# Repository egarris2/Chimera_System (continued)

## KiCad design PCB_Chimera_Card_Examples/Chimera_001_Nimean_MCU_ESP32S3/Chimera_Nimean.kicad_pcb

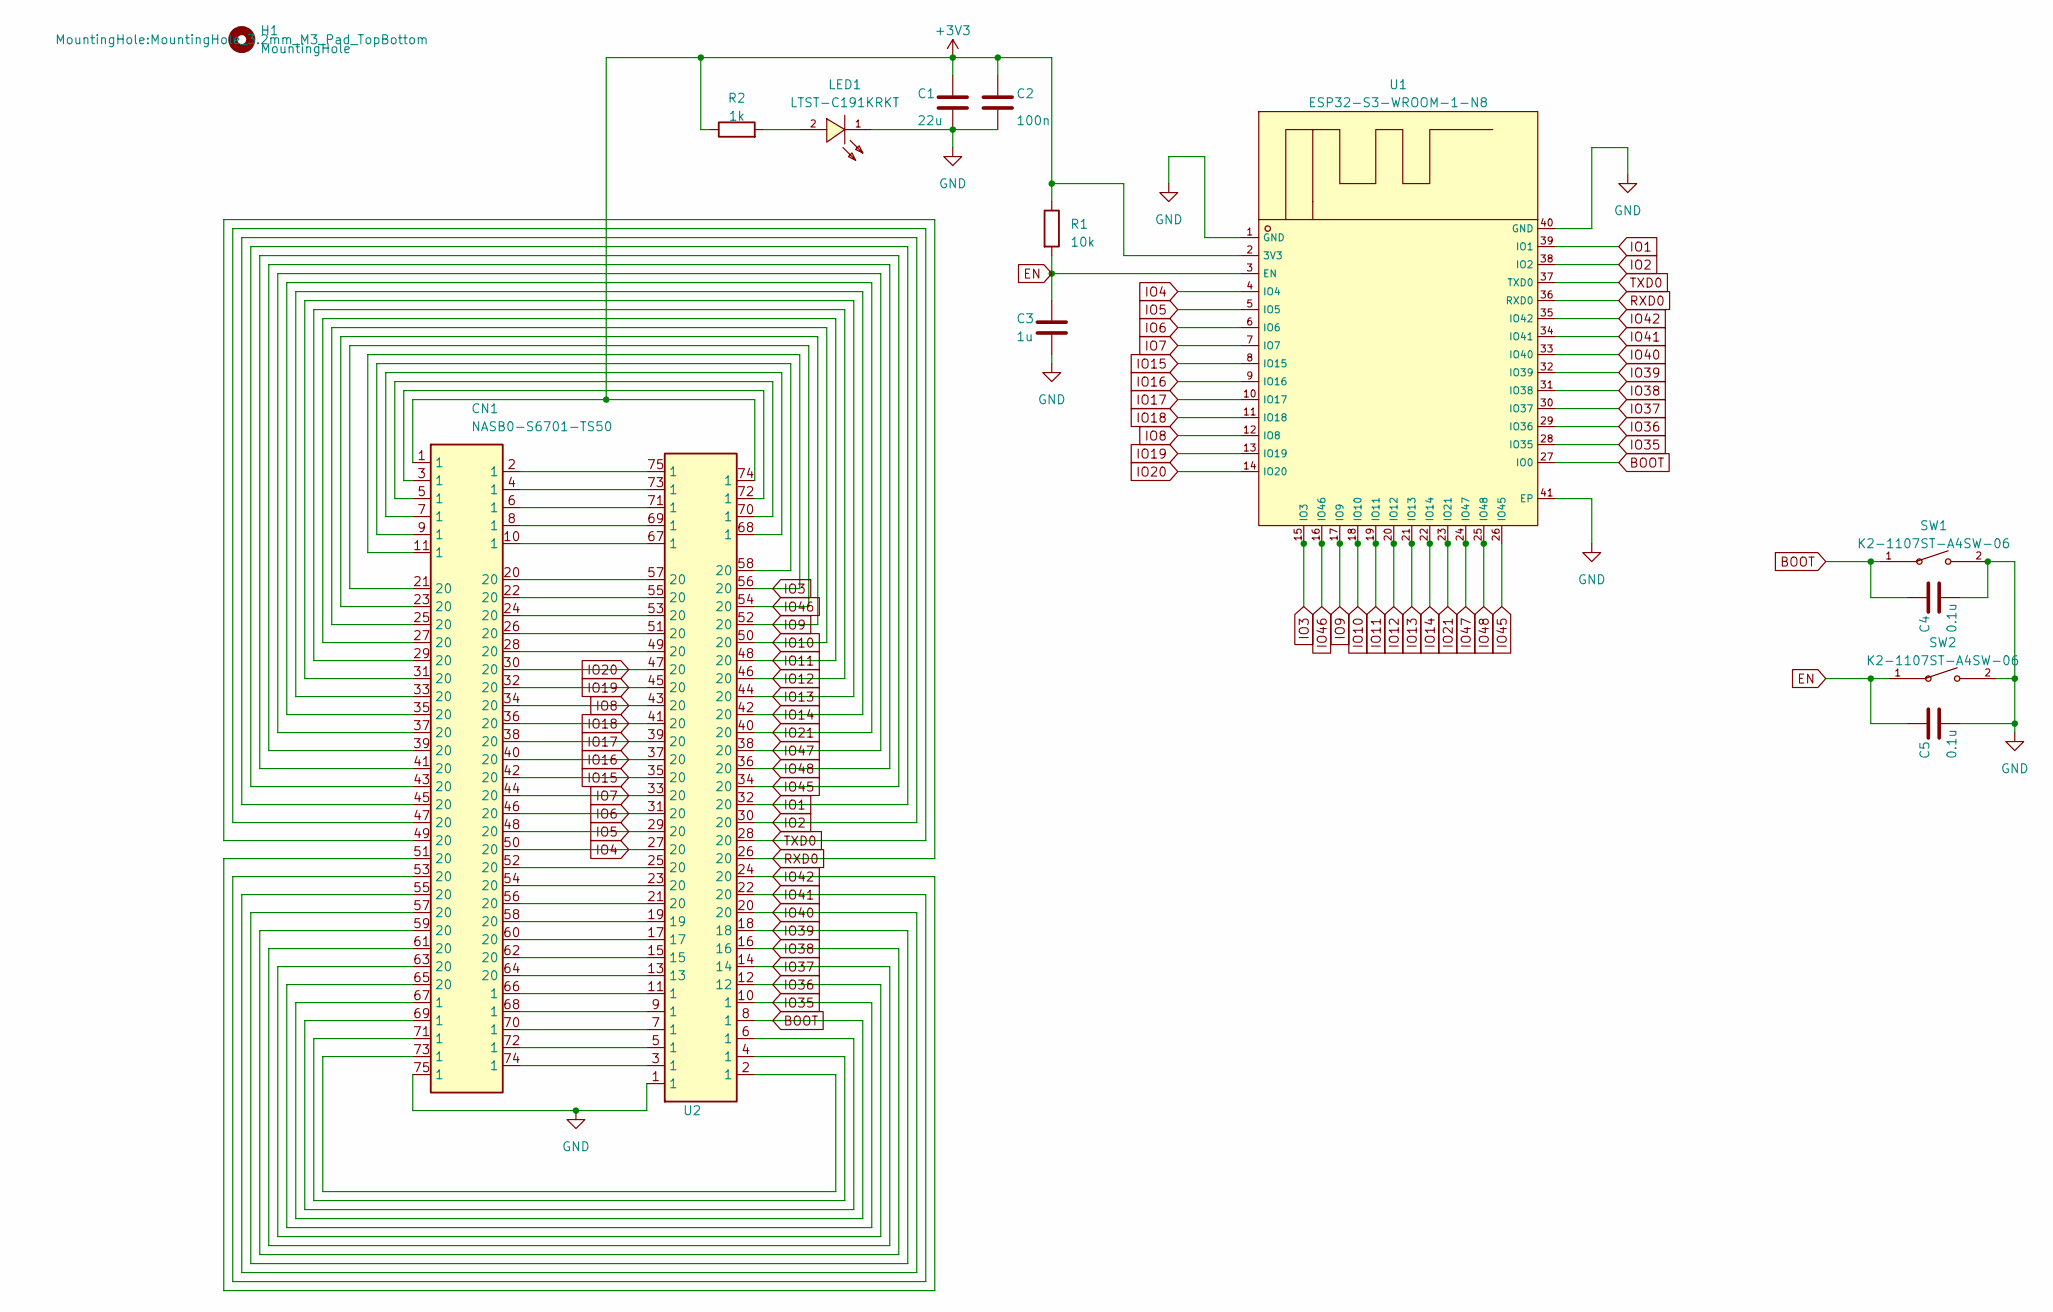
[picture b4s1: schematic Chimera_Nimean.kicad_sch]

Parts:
C1: 22u; C_0603_1608Metric
C2: 100n; C_0603_1608Metric
C3: 1u; C_0603_1608Metric
C4, C5: 0.1u; C_0603_1608Metric
CN1: NASB0-S6701-TS50; CONN-SMD_67P-P0.50-V_NASB0-S6701-TS50; LCSC C367024
H1: MountingHole; MountingHole_3.2mm_M3_Pad_TopBottom
LED1: LTST-C191KRKT; LED0603-RD; LCSC C125099
R1: 10k; R_0603_1608Metric
R2: 1k; R_0603_1608Metric
SW1, SW2: K2-1107ST-A4SW-06; KEY-SMD_L6.2-W3.6-LS8.0; LCSC C118141
U1: ESP32-S3-WROOM-1-N8; WIFIM-SMD_ESP32-S3-WROOM-1-N8; LCSC C2913198
U2: NGFF_M

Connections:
+3V3: C1.1, C2.1, CN1.1, R1.1, R2.1, U1.2 (3V3), U2.74 (1)
BOOT: C4.1, CN1.67 (1), SW1.1, U1.27 (IO0), U2.8 (1)
EN: C3.1, C5.1, R1.2, SW2.1, U1.3 (EN)
GND: C1.2, C2.2, C3.2, C4.2, C5.2, CN1.75 (1), LED1.1 (-), SW1.2, SW2.2, U1.1 (GND), U1.40 (GND), U1.41 (EP), U2.1
IO1: CN1.43 (20), U1.39 (IO1), U2.32 (20)
IO2: CN1.45 (20), U1.38 (IO2), U2.30 (20)
IO3: CN1.11 (1), U1.15 (IO3), U2.56 (20)
IO4: CN1.50 (20), U1.4 (IO4), U2.27 (20)
IO5: CN1.48 (20), U1.5 (IO5), U2.29 (20)
IO6: CN1.46 (20), U1.6 (IO6), U2.31 (20)
IO7: CN1.44 (20), U1.7 (IO7), U2.33 (20)
IO8: CN1.34 (20), U1.12 (IO8), U2.43 (20)
IO9: CN1.23 (20), U1.17 (IO9), U2.52 (20)
IO10: CN1.25 (20), U1.18 (IO10), U2.50 (20)
IO11: CN1.27 (20), U1.19 (IO11), U2.48 (20)
IO12: CN1.29 (20), U1.20 (IO12), U2.46 (20)
IO13: CN1.31 (20), U1.21 (IO13), U2.44 (20)
IO14: CN1.33 (20), U1.22 (IO14), U2.42 (20)
IO15: CN1.42 (20), U1.8 (IO15), U2.35 (20)
IO16: CN1.40 (20), U1.9 (IO16), U2.37 (20)
IO17: CN1.38 (20), U1.10 (IO17), U2.39 (20)
IO18: CN1.36 (20), U1.11 (IO18), U2.41 (20)
IO19: CN1.32 (20), U1.13 (IO19), U2.45 (20)
IO20: CN1.30 (20), U1.14 (IO20), U2.47 (20)
IO21: CN1.35 (20), U1.23 (IO21), U2.40 (20)
IO35: CN1.65 (20), U1.28 (IO35), U2.10 (1)
IO36: CN1.63 (20), U1.29 (IO36), U2.12
IO37: CN1.61 (20), U1.30 (IO37), U2.14
IO38: CN1.59 (20), U1.31 (IO38), U2.16
IO39: CN1.57 (20), U1.32 (IO39), U2.18
IO40: CN1.55 (20), U1.33 (IO40), U2.20
IO41: CN1.53 (20), U1.34 (IO41), U2.22 (20)
IO42: CN1.51 (20), U1.35 (IO42), U2.24 (20)
IO45: CN1.41 (20), U1.26 (IO45), U2.34 (20)
IO46: CN1.21 (20), U1.16 (IO46), U2.54 (20)
IO47: CN1.37 (20), U1.24 (IO47), U2.38 (20)
IO48: CN1.39 (20), U1.25 (IO48), U2.36 (20)
unnamed: CN1.2 (1), U2.75 (1)
unnamed: CN1.3 (1), U2.72 (1)
unnamed: CN1.4 (1), U2.73 (1)
unnamed: CN1.5 (1), U2.70 (1)
unnamed: CN1.6 (1), U2.71 (1)
unnamed: CN1.7 (1), U2.68 (1)
unnamed: CN1.8 (1), U2.69 (1)
unnamed: CN1.9 (1), U2.58 (20)
unnamed: CN1.10 (1), U2.67 (1)
unnamed: CN1.66 (1), U2.11 (1)
unnamed: CN1.68 (1), U2.9 (1)
unnamed: CN1.69 (1), U2.6 (1)
unnamed: CN1.70 (1), U2.7 (1)
unnamed: CN1.71 (1), U2.4 (1)
unnamed: CN1.72 (1), U2.5 (1)
unnamed: CN1.73 (1), U2.2 (1)
unnamed: CN1.74 (1), U2.3 (1)
unnamed: CN1.22 (20), U2.55 (20)
unnamed: CN1.24 (20), U2.53 (20)
unnamed: CN1.26 (20), U2.51 (20)
unnamed: CN1.28 (20), U2.49 (20)
unnamed: CN1.52 (20), U2.25 (20)
unnamed: CN1.54 (20), U2.23 (20)
unnamed: CN1.56 (20), U2.21 (20)
unnamed: CN1.58 (20), U2.19
unnamed: CN1.60 (20), U2.17
unnamed: CN1.62 (20), U2.15
unnamed: CN1.64 (20), U2.13
unnamed: CN1.20, U2.57 (20)
unnamed: LED1.2 (+), R2.2
RXD0: CN1.49 (20), U1.36 (RXD0), U2.26 (20)
TXD0: CN1.47 (20), U1.37 (TXD0), U2.28 (20)

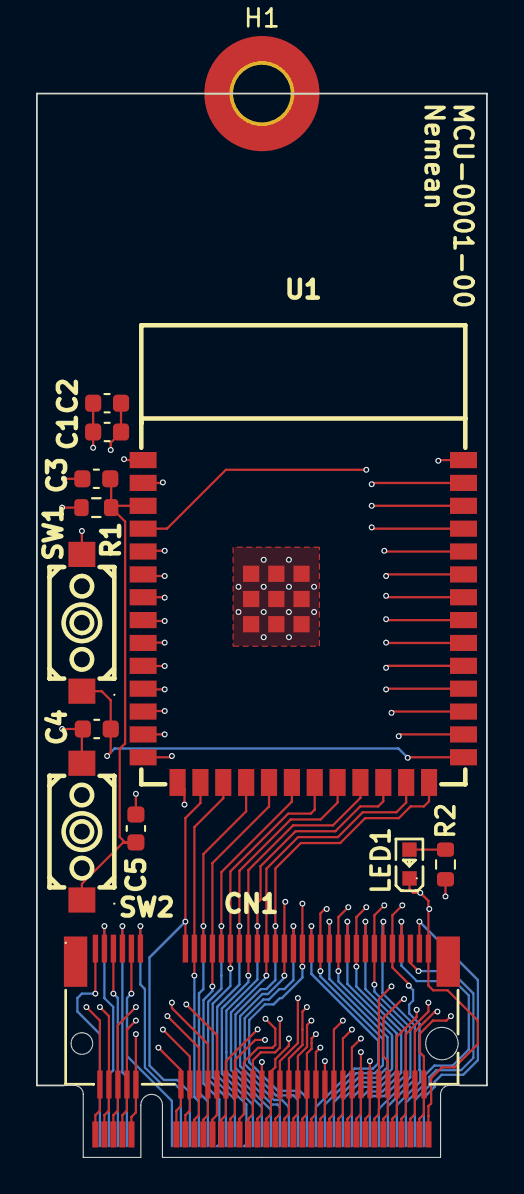
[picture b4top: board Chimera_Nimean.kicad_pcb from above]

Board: 4 copper layers, 25.0 x 59.1 mm, 14 parts (0 on the bottom side), 69 nets.

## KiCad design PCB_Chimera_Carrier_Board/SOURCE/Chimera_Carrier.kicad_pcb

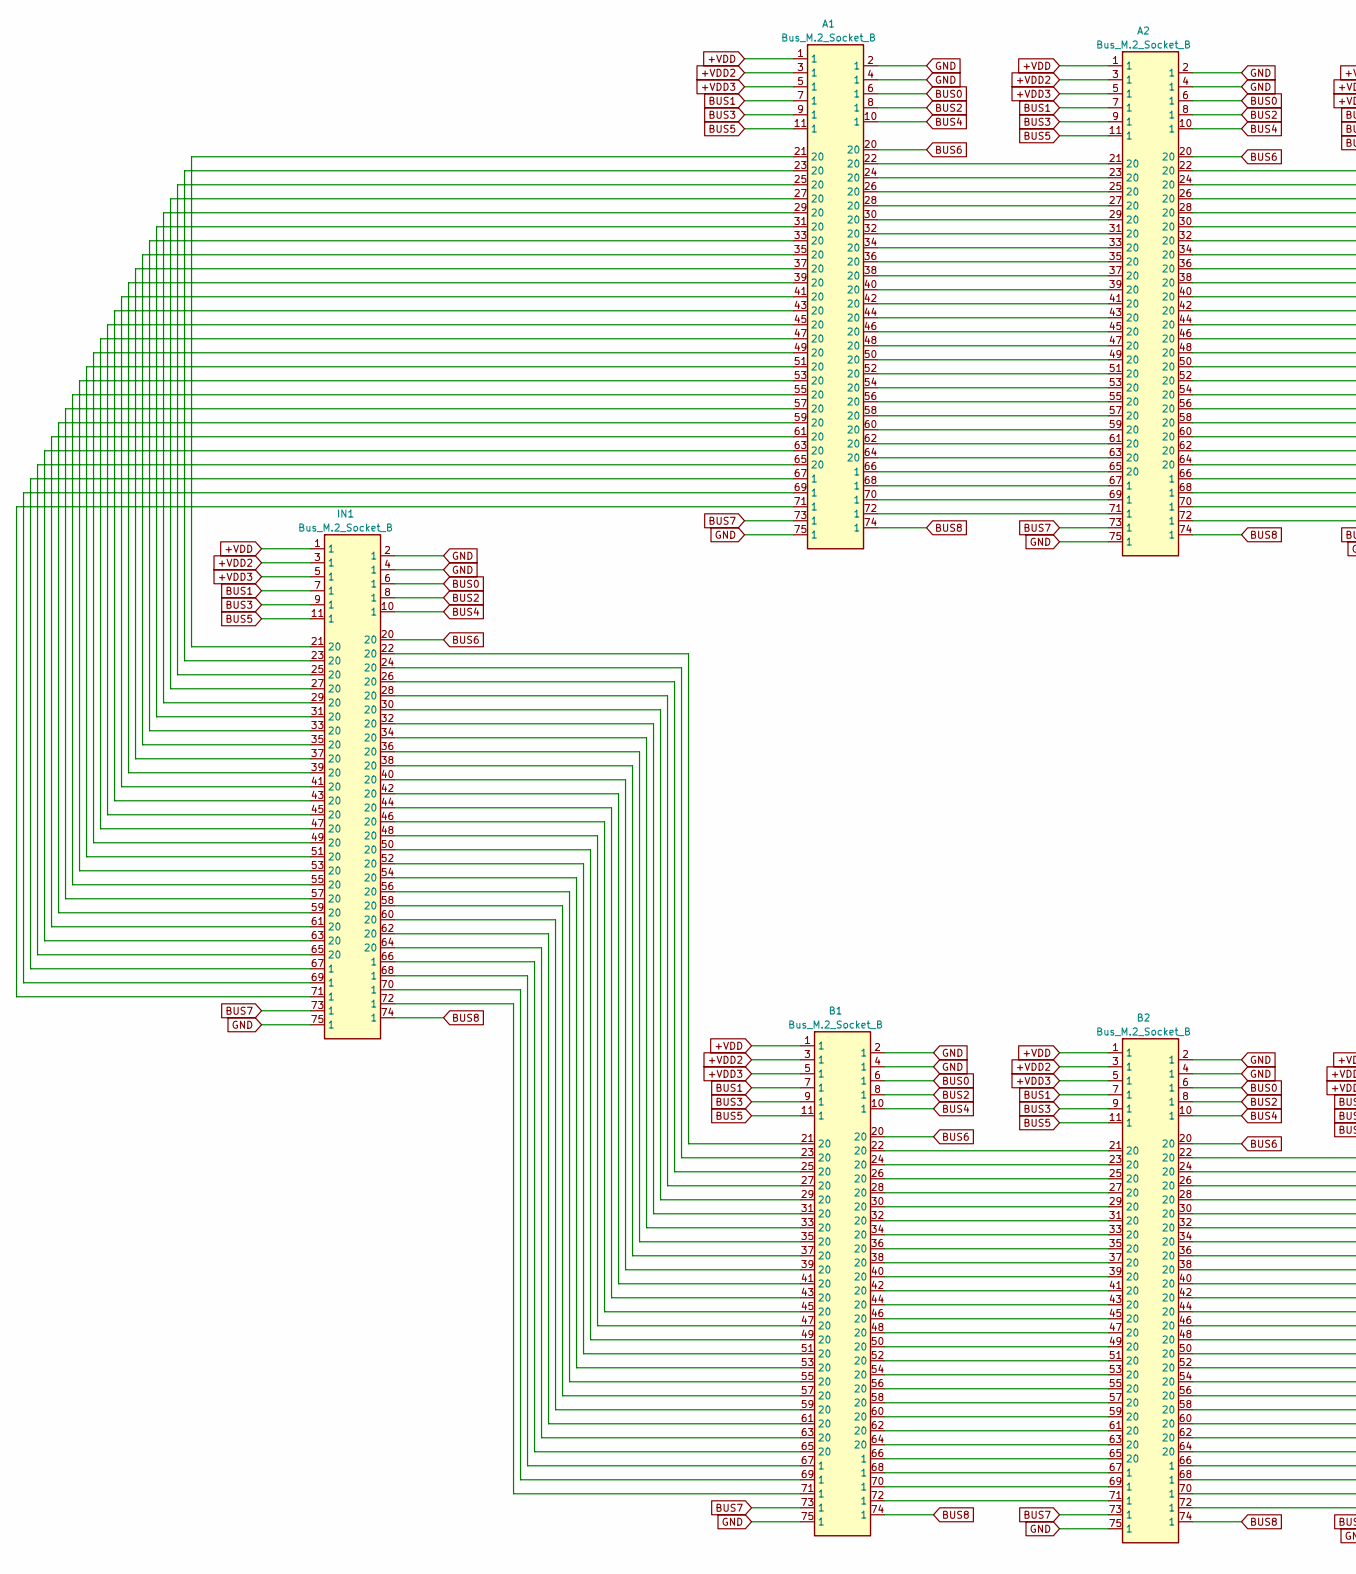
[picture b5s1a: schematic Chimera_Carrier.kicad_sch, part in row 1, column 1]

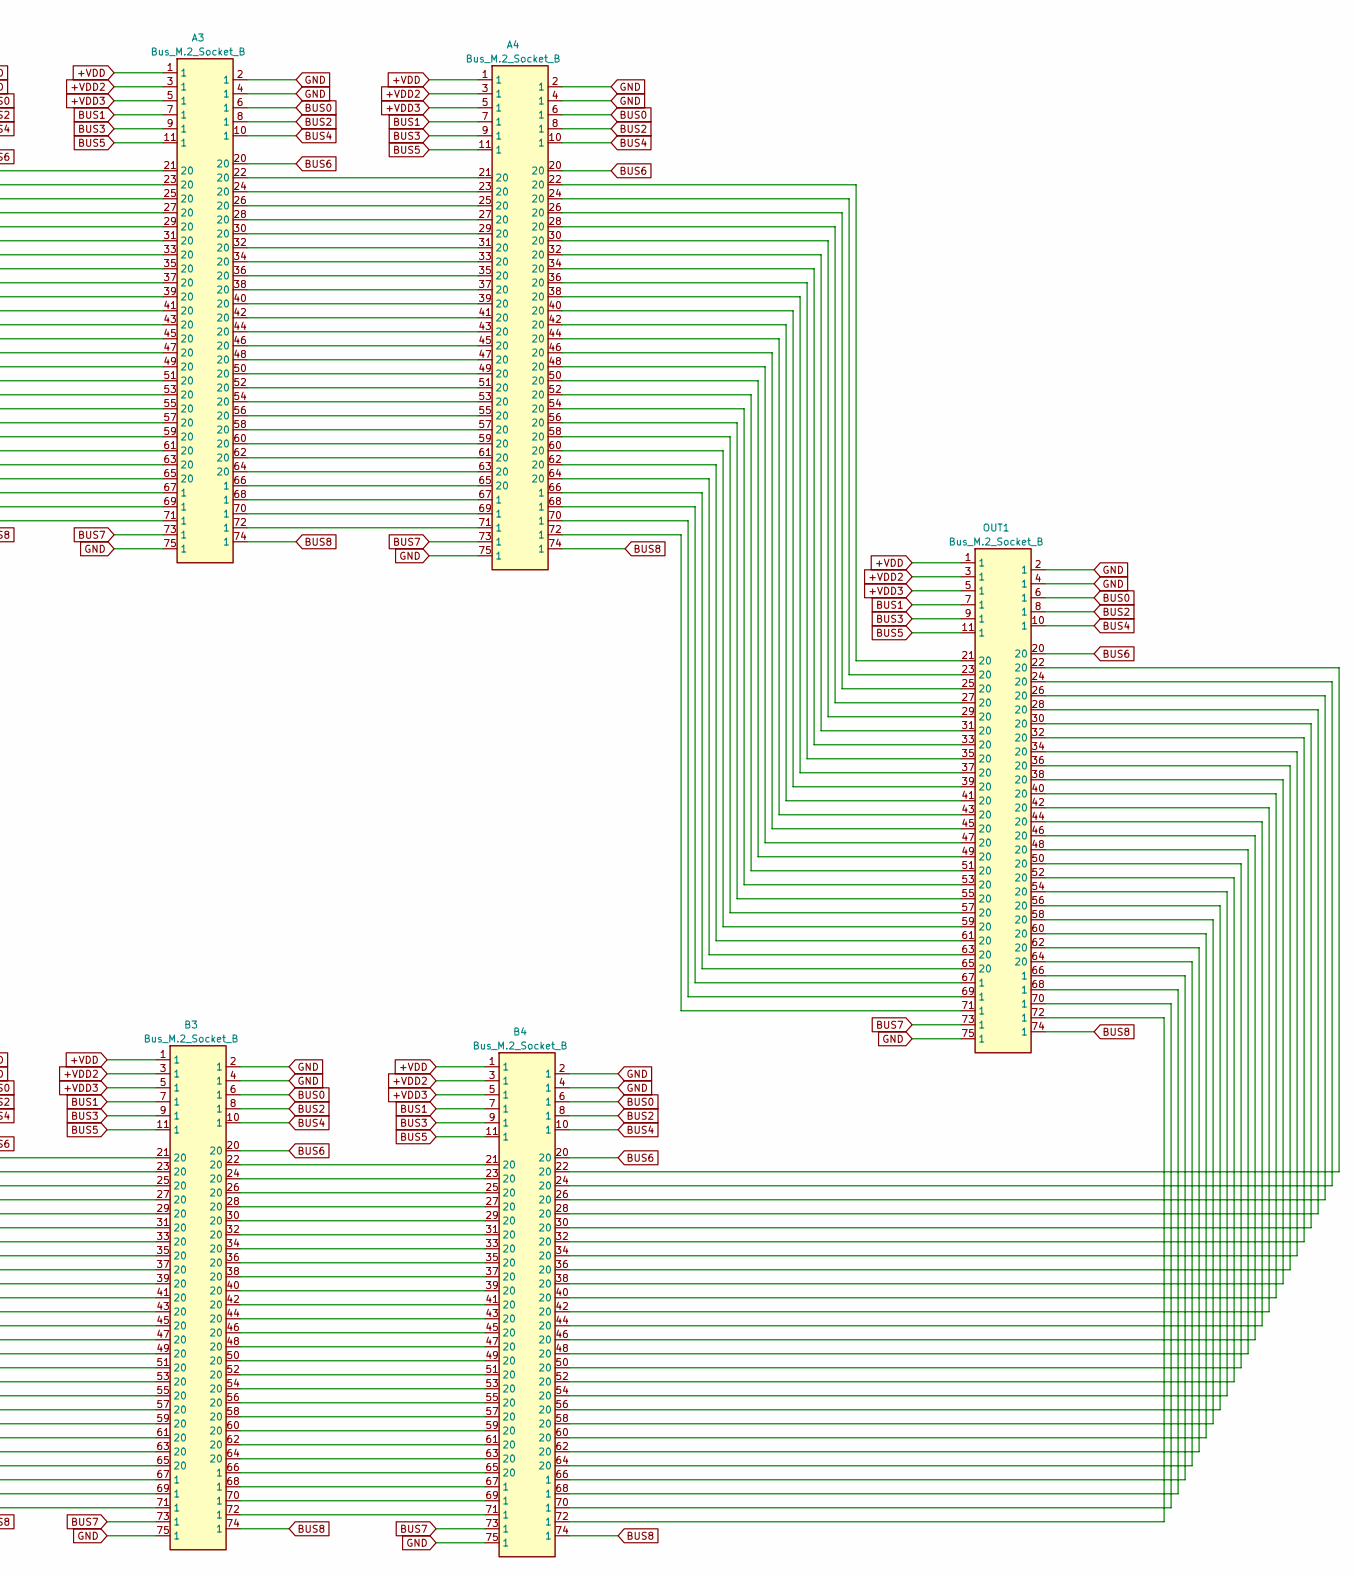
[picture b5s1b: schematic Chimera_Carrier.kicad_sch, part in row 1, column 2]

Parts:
A1, A2, A3, A4: Bus_M.2_Socket_B; NGFF_B
B1, B2, B3, B4: Bus_M.2_Socket_B; NGFF_B
IN1: Bus_M.2_Socket_B; NGFF_B
OUT1: Bus_M.2_Socket_B; NGFF_B

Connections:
+VDD: A1.1, A2.1, A3.1, A4.1, B1.1, B2.1, B3.1, B4.1, IN1.1, OUT1.1
+VDD2: A1.3 (1), A2.3 (1), A3.3 (1), A4.3 (1), B1.3 (1), B2.3 (1), B3.3 (1), B4.3 (1), IN1.3 (1), OUT1.3 (1)
+VDD3: A1.5 (1), A2.5 (1), A3.5 (1), A4.5 (1), B1.5 (1), B2.5 (1), B3.5 (1), B4.5 (1), IN1.5 (1), OUT1.5 (1)
BUS0: A1.6 (1), A2.6 (1), A3.6 (1), A4.6 (1), B1.6 (1), B2.6 (1), B3.6 (1), B4.6 (1), IN1.6 (1), OUT1.6 (1)
BUS1: A1.7 (1), A2.7 (1), A3.7 (1), A4.7 (1), B1.7 (1), B2.7 (1), B3.7 (1), B4.7 (1), IN1.7 (1), OUT1.7 (1)
BUS2: A1.8 (1), A2.8 (1), A3.8 (1), A4.8 (1), B1.8 (1), B2.8 (1), B3.8 (1), B4.8 (1), IN1.8 (1), OUT1.8 (1)
BUS3: A1.9 (1), A2.9 (1), A3.9 (1), A4.9 (1), B1.9 (1), B2.9 (1), B3.9 (1), B4.9 (1), IN1.9 (1), OUT1.9 (1)
BUS4: A1.10 (1), A2.10 (1), A3.10 (1), A4.10 (1), B1.10 (1), B2.10 (1), B3.10 (1), B4.10 (1), IN1.10 (1), OUT1.10 (1)
BUS5: A1.11 (1), A2.11 (1), A3.11 (1), A4.11 (1), B1.11 (1), B2.11 (1), B3.11 (1), B4.11 (1), IN1.11 (1), OUT1.11 (1)
BUS7: A1.73 (1), A2.73 (1), A3.73 (1), A4.73 (1), B1.73 (1), B2.73 (1), B3.73 (1), B4.73 (1), IN1.73 (1), OUT1.73 (1)
BUS8: A1.74 (1), A2.74 (1), A3.74 (1), A4.74 (1), B1.74 (1), B2.74 (1), B3.74 (1), B4.74 (1), IN1.74 (1), OUT1.74 (1)
GND: A1.2 (1), A1.4 (1), A1.75 (1), A2.2 (1), A2.4 (1), A2.75 (1), A3.2 (1), A3.4 (1), A3.75 (1), A4.2 (1), A4.4 (1), A4.75 (1), B1.2 (1), B1.4 (1), B1.75 (1), B2.2 (1), B2.4 (1), B2.75 (1), B3.2 (1), B3.4 (1), B3.75 (1), B4.2 (1), B4.4 (1), B4.75 (1), IN1.2 (1), IN1.4 (1), IN1.75 (1), OUT1.2 (1), OUT1.4 (1), OUT1.75 (1)
unnamed: A1.66 (1), A2.65 (20)
unnamed: A1.67 (1), IN1.67 (1)
unnamed: A1.68 (1), A2.67 (1)
unnamed: A1.69 (1), IN1.69 (1)
unnamed: A1.70 (1), A2.69 (1)
unnamed: A1.71 (1), IN1.71 (1)
unnamed: A1.72 (1), A2.71 (1)
unnamed: A1.21 (20), IN1.21 (20)
unnamed: A1.22 (20), A2.21 (20)
unnamed: A1.23 (20), IN1.23 (20)
unnamed: A1.24 (20), A2.23 (20)
unnamed: A1.25 (20), IN1.25 (20)
unnamed: A1.26 (20), A2.25 (20)
unnamed: A1.27 (20), IN1.27 (20)
unnamed: A1.28 (20), A2.27 (20)
unnamed: A1.29 (20), IN1.29 (20)
unnamed: A1.30 (20), A2.29 (20)
unnamed: A1.31 (20), IN1.31 (20)
unnamed: A1.32 (20), A2.31 (20)
unnamed: A1.33 (20), IN1.33 (20)
unnamed: A1.34 (20), A2.33 (20)
unnamed: A1.35 (20), IN1.35 (20)
unnamed: A1.36 (20), A2.35 (20)
unnamed: A1.37 (20), IN1.37 (20)
unnamed: A1.38 (20), A2.37 (20)
unnamed: A1.39 (20), IN1.39 (20)
unnamed: A1.40 (20), A2.39 (20)
unnamed: A1.41 (20), IN1.41 (20)
unnamed: A1.42 (20), A2.41 (20)
unnamed: A1.43 (20), IN1.43 (20)
unnamed: A1.44 (20), A2.43 (20)
unnamed: A1.45 (20), IN1.45 (20)
unnamed: A1.46 (20), A2.45 (20)
unnamed: A1.47 (20), IN1.47 (20)
unnamed: A1.48 (20), A2.47 (20)
unnamed: A1.49 (20), IN1.49 (20)
unnamed: A1.50 (20), A2.49 (20)
unnamed: A1.51 (20), IN1.51 (20)
unnamed: A1.52 (20), A2.51 (20)
unnamed: A1.53 (20), IN1.53 (20)
unnamed: A1.54 (20), A2.53 (20)
unnamed: A1.55 (20), IN1.55 (20)
unnamed: A1.56 (20), A2.55 (20)
unnamed: A1.57 (20), IN1.57 (20)
unnamed: A1.58 (20), A2.57 (20)
unnamed: A1.59 (20), IN1.59 (20)
unnamed: A1.60 (20), A2.59 (20)
unnamed: A1.61 (20), IN1.61 (20)
unnamed: A1.62 (20), A2.61 (20)
unnamed: A1.63 (20), IN1.63 (20)
unnamed: A1.64 (20), A2.63 (20)
unnamed: A1.65 (20), IN1.65 (20)
unnamed: A2.66 (1), A3.65 (20)
unnamed: A2.68 (1), A3.67 (1)
unnamed: A2.70 (1), A3.69 (1)
unnamed: A2.72 (1), A3.71 (1)
unnamed: A2.22 (20), A3.21 (20)
unnamed: A2.24 (20), A3.23 (20)
unnamed: A2.26 (20), A3.25 (20)
unnamed: A2.28 (20), A3.27 (20)
unnamed: A2.30 (20), A3.29 (20)
unnamed: A2.32 (20), A3.31 (20)
unnamed: A2.34 (20), A3.33 (20)
unnamed: A2.36 (20), A3.35 (20)
unnamed: A2.38 (20), A3.37 (20)
unnamed: A2.40 (20), A3.39 (20)
unnamed: A2.42 (20), A3.41 (20)
unnamed: A2.44 (20), A3.43 (20)
unnamed: A2.46 (20), A3.45 (20)
unnamed: A2.48 (20), A3.47 (20)
unnamed: A2.50 (20), A3.49 (20)
unnamed: A2.52 (20), A3.51 (20)
unnamed: A2.54 (20), A3.53 (20)
unnamed: A2.56 (20), A3.55 (20)
unnamed: A2.58 (20), A3.57 (20)
unnamed: A2.60 (20), A3.59 (20)
unnamed: A2.62 (20), A3.61 (20)
unnamed: A2.64 (20), A3.63 (20)
unnamed: A3.66 (1), A4.65 (20)
unnamed: A3.68 (1), A4.67 (1)
unnamed: A3.70 (1), A4.69 (1)
unnamed: A3.72 (1), A4.71 (1)
unnamed: A3.22 (20), A4.21 (20)
unnamed: A3.24 (20), A4.23 (20)
unnamed: A3.26 (20), A4.25 (20)
unnamed: A3.28 (20), A4.27 (20)
unnamed: A3.30 (20), A4.29 (20)
unnamed: A3.32 (20), A4.31 (20)
unnamed: A3.34 (20), A4.33 (20)
unnamed: A3.36 (20), A4.35 (20)
unnamed: A3.38 (20), A4.37 (20)
unnamed: A3.40 (20), A4.39 (20)
unnamed: A3.42 (20), A4.41 (20)
unnamed: A3.44 (20), A4.43 (20)
unnamed: A3.46 (20), A4.45 (20)
unnamed: A3.48 (20), A4.47 (20)
unnamed: A3.50 (20), A4.49 (20)
unnamed: A3.52 (20), A4.51 (20)
unnamed: A3.54 (20), A4.53 (20)
unnamed: A3.56 (20), A4.55 (20)
unnamed: A3.58 (20), A4.57 (20)
unnamed: A3.60 (20), A4.59 (20)
unnamed: A3.62 (20), A4.61 (20)
unnamed: A3.64 (20), A4.63 (20)
unnamed: A4.66 (1), OUT1.65 (20)
unnamed: A4.68 (1), OUT1.67 (1)
unnamed: A4.70 (1), OUT1.69 (1)
unnamed: A4.72 (1), OUT1.71 (1)
unnamed: A4.22 (20), OUT1.21 (20)
unnamed: A4.24 (20), OUT1.23 (20)
unnamed: A4.26 (20), OUT1.25 (20)
unnamed: A4.28 (20), OUT1.27 (20)
unnamed: A4.30 (20), OUT1.29 (20)
unnamed: A4.32 (20), OUT1.31 (20)
unnamed: A4.34 (20), OUT1.33 (20)
unnamed: A4.36 (20), OUT1.35 (20)
unnamed: A4.38 (20), OUT1.37 (20)
unnamed: A4.40 (20), OUT1.39 (20)
unnamed: A4.42 (20), OUT1.41 (20)
unnamed: A4.44 (20), OUT1.43 (20)
unnamed: A4.46 (20), OUT1.45 (20)
unnamed: A4.48 (20), OUT1.47 (20)
unnamed: A4.50 (20), OUT1.49 (20)
unnamed: A4.52 (20), OUT1.51 (20)
unnamed: A4.54 (20), OUT1.53 (20)
unnamed: A4.56 (20), OUT1.55 (20)
unnamed: A4.58 (20), OUT1.57 (20)
unnamed: A4.60 (20), OUT1.59 (20)
unnamed: A4.62 (20), OUT1.61 (20)
unnamed: A4.64 (20), OUT1.63 (20)
unnamed: B1.66 (1), B2.65 (20)
unnamed: B1.67 (1), IN1.68 (1)
unnamed: B1.68 (1), B2.67 (1)
unnamed: B1.69 (1), IN1.70 (1)
unnamed: B1.70 (1), B2.69 (1)
unnamed: B1.71 (1), IN1.72 (1)
unnamed: B1.72 (1), B2.71 (1)
unnamed: B1.21 (20), IN1.22 (20)
unnamed: B1.22 (20), B2.21 (20)
unnamed: B1.23 (20), IN1.24 (20)
unnamed: B1.24 (20), B2.23 (20)
unnamed: B1.25 (20), IN1.26 (20)
unnamed: B1.26 (20), B2.25 (20)
unnamed: B1.27 (20), IN1.28 (20)
unnamed: B1.28 (20), B2.27 (20)
unnamed: B1.29 (20), IN1.30 (20)
unnamed: B1.30 (20), B2.29 (20)
unnamed: B1.31 (20), IN1.32 (20)
unnamed: B1.32 (20), B2.31 (20)
unnamed: B1.33 (20), IN1.34 (20)
unnamed: B1.34 (20), B2.33 (20)
unnamed: B1.35 (20), IN1.36 (20)
unnamed: B1.36 (20), B2.35 (20)
unnamed: B1.37 (20), IN1.38 (20)
unnamed: B1.38 (20), B2.37 (20)
unnamed: B1.39 (20), IN1.40 (20)
unnamed: B1.40 (20), B2.39 (20)
unnamed: B1.41 (20), IN1.42 (20)
unnamed: B1.42 (20), B2.41 (20)
unnamed: B1.43 (20), IN1.44 (20)
unnamed: B1.44 (20), B2.43 (20)
unnamed: B1.45 (20), IN1.46 (20)
unnamed: B1.46 (20), B2.45 (20)
unnamed: B1.47 (20), IN1.48 (20)
unnamed: B1.48 (20), B2.47 (20)
unnamed: B1.49 (20), IN1.50 (20)
unnamed: B1.50 (20), B2.49 (20)
unnamed: B1.51 (20), IN1.52 (20)
unnamed: B1.52 (20), B2.51 (20)
unnamed: B1.53 (20), IN1.54 (20)
unnamed: B1.54 (20), B2.53 (20)
unnamed: B1.55 (20), IN1.56 (20)
unnamed: B1.56 (20), B2.55 (20)
unnamed: B1.57 (20), IN1.58 (20)
unnamed: B1.58 (20), B2.57 (20)
unnamed: B1.59 (20), IN1.60 (20)
unnamed: B1.60 (20), B2.59 (20)
unnamed: B1.61 (20), IN1.62 (20)
unnamed: B1.62 (20), B2.61 (20)
unnamed: B1.63 (20), IN1.64 (20)
unnamed: B1.64 (20), B2.63 (20)
unnamed: B1.65 (20), IN1.66 (1)
unnamed: B2.66 (1), B3.65 (20)
unnamed: B2.68 (1), B3.67 (1)
unnamed: B2.70 (1), B3.69 (1)
unnamed: B2.22 (20), B3.21 (20)
unnamed: B2.24 (20), B3.23 (20)
unnamed: B2.26 (20), B3.25 (20)
unnamed: B2.28 (20), B3.27 (20)
unnamed: B2.30 (20), B3.29 (20)
unnamed: B2.32 (20), B3.31 (20)
unnamed: B2.34 (20), B3.33 (20)
unnamed: B2.36 (20), B3.35 (20)
unnamed: B2.38 (20), B3.37 (20)
unnamed: B2.40 (20), B3.39 (20)
unnamed: B2.42 (20), B3.41 (20)
unnamed: B2.44 (20), B3.43 (20)
unnamed: B2.46 (20), B3.45 (20)
unnamed: B2.48 (20), B3.47 (20)
unnamed: B2.50 (20), B3.49 (20)
unnamed: B2.52 (20), B3.51 (20)
unnamed: B2.54 (20), B3.53 (20)
unnamed: B2.56 (20), B3.55 (20)
unnamed: B2.58 (20), B3.57 (20)
unnamed: B2.60 (20), B3.59 (20)
unnamed: B2.62 (20), B3.61 (20)
unnamed: B2.64 (20), B3.63 (20)
unnamed: B3.66 (1), B4.65 (20)
unnamed: B3.68 (1), B4.67 (1)
unnamed: B3.70 (1), B4.69 (1)
unnamed: B3.72 (1), B4.71 (1)
unnamed: B3.22 (20), B4.21 (20)
unnamed: B3.24 (20), B4.23 (20)
unnamed: B3.26 (20), B4.25 (20)
unnamed: B3.28 (20), B4.27 (20)
unnamed: B3.30 (20), B4.29 (20)
unnamed: B3.32 (20), B4.31 (20)
unnamed: B3.34 (20), B4.33 (20)
unnamed: B3.36 (20), B4.35 (20)
unnamed: B3.38 (20), B4.37 (20)
unnamed: B3.40 (20), B4.39 (20)
unnamed: B3.42 (20), B4.41 (20)
unnamed: B3.44 (20), B4.43 (20)
unnamed: B3.46 (20), B4.45 (20)
unnamed: B3.48 (20), B4.47 (20)
unnamed: B3.50 (20), B4.49 (20)
unnamed: B3.52 (20), B4.51 (20)
unnamed: B3.54 (20), B4.53 (20)
unnamed: B3.56 (20), B4.55 (20)
unnamed: B3.58 (20), B4.57 (20)
unnamed: B3.60 (20), B4.59 (20)
unnamed: B3.62 (20), B4.61 (20)
unnamed: B3.64 (20), B4.63 (20)
unnamed: B4.66 (1), OUT1.66 (1)
unnamed: B4.68 (1), OUT1.68 (1)
unnamed: B4.70 (1), OUT1.70 (1)
unnamed: B4.72 (1), OUT1.72 (1)
unnamed: B4.22 (20), OUT1.22 (20)
unnamed: B4.24 (20), OUT1.24 (20)
unnamed: B4.26 (20), OUT1.26 (20)
unnamed: B4.28 (20), OUT1.28 (20)
unnamed: B4.30 (20), OUT1.30 (20)
unnamed: B4.32 (20), OUT1.32 (20)
unnamed: B4.34 (20), OUT1.34 (20)
unnamed: B4.36 (20), OUT1.36 (20)
unnamed: B4.38 (20), OUT1.38 (20)
unnamed: B4.40 (20), OUT1.40 (20)
unnamed: B4.42 (20), OUT1.42 (20)
unnamed: B4.44 (20), OUT1.44 (20)
unnamed: B4.46 (20), OUT1.46 (20)
unnamed: B4.48 (20), OUT1.48 (20)
unnamed: B4.50 (20), OUT1.50 (20)
unnamed: B4.52 (20), OUT1.52 (20)
unnamed: B4.54 (20), OUT1.54 (20)
unnamed: B4.56 (20), OUT1.56 (20)
unnamed: B4.58 (20), OUT1.58 (20)
unnamed: B4.60 (20), OUT1.60 (20)
unnamed: B4.62 (20), OUT1.62 (20)
unnamed: B4.64 (20), OUT1.64 (20)

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
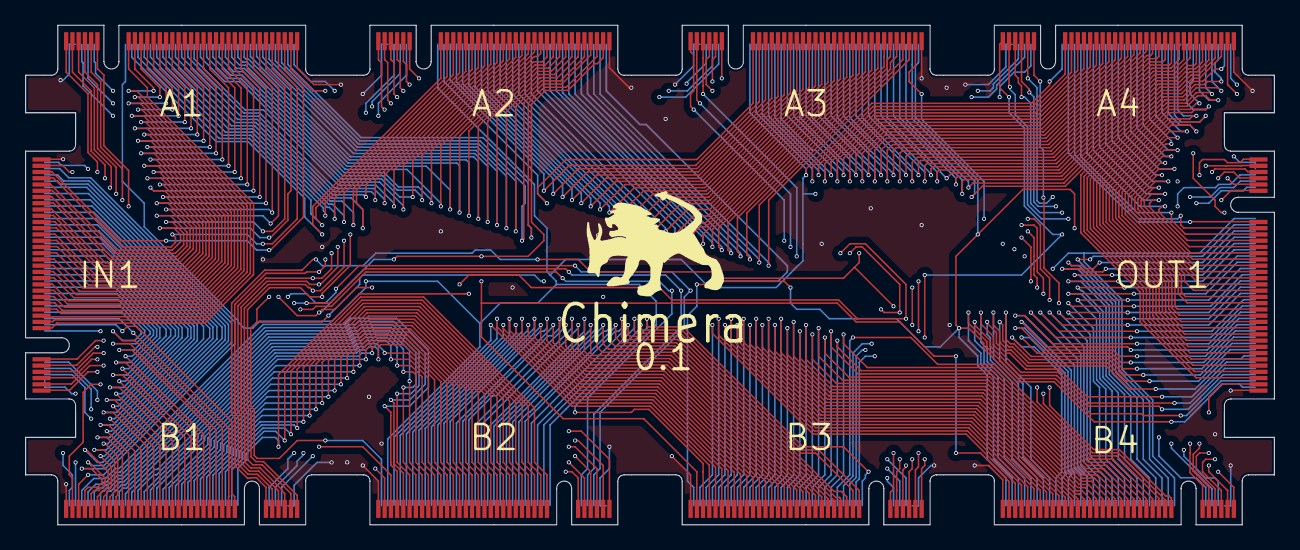
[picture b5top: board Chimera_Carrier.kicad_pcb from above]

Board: 4 copper layers, 100.0 x 40.0 mm, 11 parts (0 on the bottom side), 273 nets.

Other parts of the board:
Chimera: LOGO

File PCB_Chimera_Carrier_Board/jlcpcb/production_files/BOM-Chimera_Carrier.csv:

Comment,Designator,Footprint,LCSC
Bus_M.2_Socket_B,B1,NGFF_B,
Bus_M.2_Socket_B,A2,NGFF_B,
Bus_M.2_Socket_B,IN1,NGFF_B,
Bus_M.2_Socket_B,OUT1,NGFF_B,
Bus_M.2_Socket_B,A3,NGFF_B,
Bus_M.2_Socket_B,B3,NGFF_B,
Bus_M.2_Socket_B,B2,NGFF_B,
Bus_M.2_Socket_B,B4,NGFF_B,
Bus_M.2_Socket_B,A1,NGFF_B,
Bus_M.2_Socket_B,A4,NGFF_B,

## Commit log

2023-10-11 First commit. WORK IN PROGRESS
2023-10-11 Added image with annotations.
2023-10-11 Cleaned up folders
2023-10-11 Added Nimean Pin description document
2023-10-12 added Kicad JLC workflow document
2023-10-12 start eagle port
2023-10-12 ignore
2023-10-13 have footprints complete
2023-10-17 added board settings, including design rules, to the accessory card template board file.
2023-10-17 completed accessory card template
2023-10-18 finish mcu card template
2023-10-18 Connected air wire on pad 47 of the card_template
2023-10-18 Moved board into title block border. for Chimera_Card_template
2023-10-18 start pic24 card
2023-10-19 finished breaking out pic pins up near connector
2023-10-19 cleaned up model_chimera_card_holder folder and updated card holder model.
2023-10-19 pic24 card is done, gerbers and jlc files generated
2023-10-23 upd gitignore
2023-10-23 finish pwr supply card
2023-11-16 Backlink to CADLAB.io has been added.
